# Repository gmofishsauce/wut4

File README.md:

# Wholly Unnecessary Technologies (WUT) model 4 computer (WUT-4 or WUT4)

The content of this repo is [licensed](./LICENSE).

#
## [lang/yasm](./lang/yasm) - wut4 assembler

Assembler written in Go by Claude Code.

## [emul](./emul) - wut4 emulator

Functional emulator written in Go by Claude Code.

## [lang] (./lang) - YAPL language)

Four pass compiler written in Go by Claude Code.

## [exer/cex](./exer/cex) - chip exerciser/tester

CLI tool that communicates via USB serial with a Nano. The Nano
is configured as a chip exerciser / tester. Also in `exer` are
the KiCad schematic for the chip exerciser in `ki` and the Nano
firmware in `fw`. The firmware is a simplified version of the
YARC firmware.

## [lib](./lib)

Eventual library of I/O routines for emulated devices.

## [pld](./pld) - 22v10 experiments

Including a general 8-bit register.

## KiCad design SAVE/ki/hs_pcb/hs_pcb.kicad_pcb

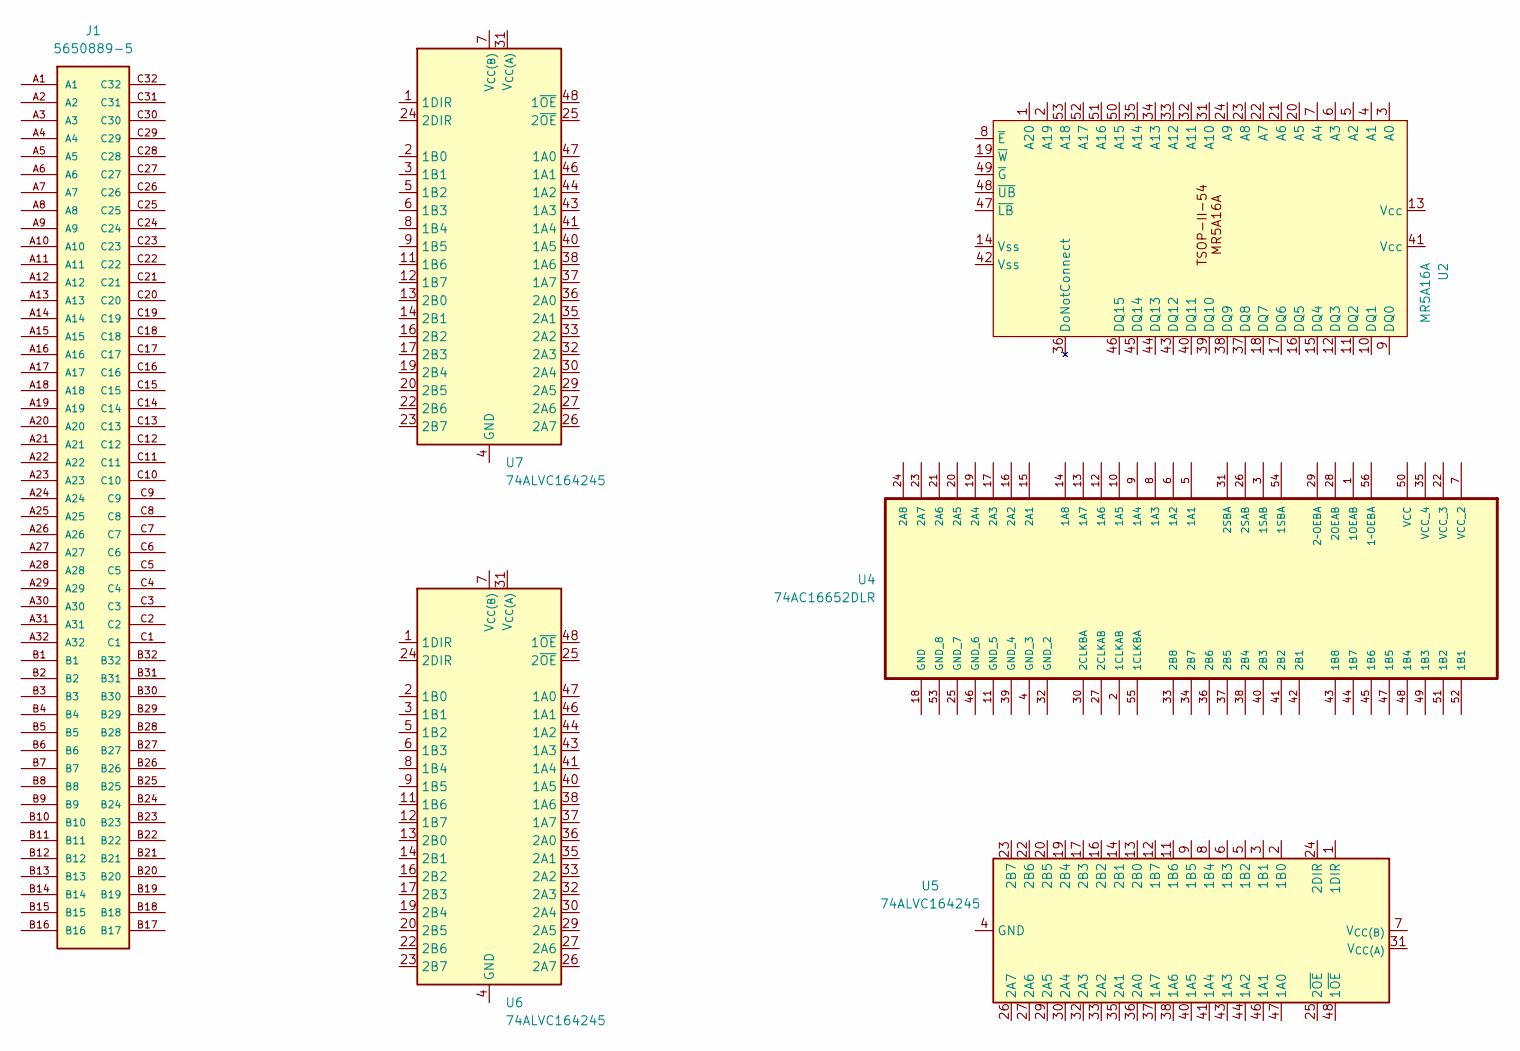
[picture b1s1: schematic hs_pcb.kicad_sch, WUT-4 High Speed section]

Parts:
J1: 5650889-5; TE_5650889-5
U2: MR5A16A; TSOP-II-54_22.2x10.16mm_P0.8mm
U4: 74AC16652DLR; SOP63P1035X279-56N; MPN 74AC16652DLR
U5, U6, U7: 74ALVC164245; TSSOP-48_6.1x12.5mm_P0.5mm

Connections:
unnamed: U5.4 (GND), U5.10 (GND), U5.15 (GND), U5.21 (GND), U5.28 (GND), U5.34 (GND), U5.39 (GND), U5.45 (GND)
unnamed: U5.31 (V_{CC(A)}), U5.42 (V_{CC(A)})
unnamed: U5.7 (V_{CC(B)}), U5.18 (V_{CC(B)})
unnamed: U6.4 (GND), U6.10 (GND), U6.15 (GND), U6.21 (GND), U6.28 (GND), U6.34 (GND), U6.39 (GND), U6.45 (GND)
unnamed: U6.31 (V_{CC(A)}), U6.42 (V_{CC(A)})
unnamed: U6.7 (V_{CC(B)}), U6.18 (V_{CC(B)})
unnamed: U7.4 (GND), U7.10 (GND), U7.15 (GND), U7.21 (GND), U7.28 (GND), U7.34 (GND), U7.39 (GND), U7.45 (GND)
unnamed: U7.31 (V_{CC(A)}), U7.42 (V_{CC(A)})
unnamed: U7.7 (V_{CC(B)}), U7.18 (V_{CC(B)})

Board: 2 copper layers, 7 parts (0 on the bottom side), 9 nets, no tracks yet.

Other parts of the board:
U3: 74AC16652DLR; SOP63P1035X279-56N

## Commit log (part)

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2024-03-11 First step in moving y4 repo to its new home here.
2024-03-11 Second step in conversion. Move assembler, disassembler, and round trip test framework (itf) from the old y4 repo to this repo. Rename disassembler from dis to dsm.
2024-03-11 Step 3 of repo conversion. Add functional emulator and rename it to emul.
2024-03-11 More cleanup on README
2024-03-12 Improve comments and READMEs. Fix call from emulator to disassembler.
2024-03-14 Interim commit - ongoing development
2024-03-15 Ongoing development
2024-03-17 Improve symbol table interface and tests based on some lexer coding. No tests for the lexer yet.
2024-03-18 Add lex_test.go and t1.yapl-1 test program. Add definitions for all the language-defined symbols. Partial implementation of printf(). Update language spec in readme. Other minor changes.
2024-03-19 Many changes required to get basic lexer test to work. Ongoing development.
2024-03-22 Begin parser implementation. Add token pushback.
2024-03-22 Add minimal error handler. Change TT_STR to TT_USR. Clean up AST node handling and add allocator function. Improve logic in first two recursive descent functions. Fix initialization for language symb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
2024-03-23 Move error definitions to error.go. Add a type Error and small functions to handle it. Parser now compiles, but not even close to working. Existing unit tests pass. Add a long comment in types.go.
2024-03-24 Implement better error handler (not tested). Further improve comments.
2024-04-04 Implement types StrIndex and SymIndex. Move code to lex.go from types.go.
2024-04-06 Replace Error type with Word. Get rid of AsError() function. Comment out most of parser and write a simple test for it.
2024-04-14 Parsed a single line after more aimless mucking about with the code
2024-04-15 Change initialization so the descriptor of the (single) source file is passed to the lexer at init and doesn't have to be passed in on each call from the parser.
2024-04-22 Initial KiCad project for wut-4. Includes 2Mx16 MRAM model with TSOP-II 54-pin footprint.
2024-05-20 Initial commit of MR5A16 model in hneeman/Digital
2024-05-25 4-bit synch counter from 1976 TTL Data Book in hnmeeman/Digital
2024-05-28 Remove KiCad backups from repo
2024-05-30 Ongoing development of chip exerciser
2024-06-01 Create exer firmware in fw/ by copying YARC firmware
2024-06-03 Continue removing YARC specifics from serial code for Nano. Begin munging golang code into a single file. FW compiles, Go code does not.
2024-06-04 Continue simplifying protocol
2024-06-04 Continue simplifying code to basic host/nano comms
2024-06-04 rename host side program
2024-06-04 Clean up comments and add cex to gitignore
2024-06-05 This version boots and talks to cex host software. Mostly done removing YARC related code.
2024-06-08 Correct schematic for wiring to the 24-pin socket
2024-06-10 Ongoing development. Nano communicates with host. t (toggle pulse output) command works.
2024-06-11 Protocol v13 adds support for bit reversed set and get. Cex parses arguments in hex now. Move bit reverser in Nano to public. Fix bad debug statement. Lightly tested, quote works endquote.
2024-06-13 Update README with docs for vector-based exerciser
2024-06-14 Hopefully-final fix to U10 control line outputs. They are now on the low-order bits and the Arduino reverses the bits in the register. Also pick up the very start of vector support in host software.
2024-06-16 Update README (still needs work). Temporarily divert main to DoVectorFile() for debugging. Much development in vector.go. Changes to U10 wiring in fact, in KiCad, in Fritzing (separate commit), and m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
2024-06-17 Split out types into separate files. Separate parseVector and applyVector from DoVectorFile. ApplyVector is TODO.
2024-06-18 Move a few things around in search of modularity
2024-06-18 Factor out functions for the t, s, and g commands to the Nano and fix a wiring error in KiCad.
2024-06-18 Reformat the world
2024-06-19 Move Arduino files to local package dev and begin work on applying vectors to hardware
2024-06-24 Correct function (s0..s2) bits in test file and fix bug in flag output processing that caused false error reports.
2024-06-28 Add a summary error count per file and report the total error count for all files. Manually check the sequential test vectors and fix them up to report success when they succeed instead of reporting 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
2024-07-05 Create a 100mm square box and add some 16-bit components
2024-07-18 Complete basic test vectors for L4C381. 4 units passed tests. Improve wiring for 24-pin ZIF socket. Also commit Fritzing changes in $YARC.
2024-07-20 Reformat all the Go code. Improve README. Add top level build script BUILD_ALL.
2024-07-20 Non-overlapping clock generator fails in Digital
2024-07-21 Implement ZIF socket support in cex. Not tested.
2024-07-22 Remove .DS_Store files and add to .gitignore
2024-07-23 Checkpoint - define a PLD and fix test code so that clock is always on pin 1 as required by 22V10 component. Not tested.
2024-07-25 Interim commit after much hardware and software troubleshooting
2024-07-25 Commit 22V574-2 component with a functional test
2024-12-16 Initial commit of new simulator
2024-12-16 Add debugging support
2025-01-23 Ongoing development of C simulator. Create simple PLD for studying 22V10 JEDED files.
2025-01-25 Simplify data structures. Compiles without warnings.
2025-01-25 Freezing sim for more thought
2025-03-02 Move earlier simulators to SAVE/. Add SCsim and learning file first.cpp.
2025-03-03 AI-assisted learning experiment for SystemC simulator
2025-03-18 Give up on SystemC and pull C simulator back out of SAVE/
2025-03-18 Correct previous commit
2025-05-09 Ongoing thinking
2025-05-13 Ongoing work implementing netlist parser for KiCad schematics
2025-05-14 Code now builds and dumps a tree of ModelNodes
2025-05-15 Add a couple of test exports and improve generated top comment
2025-05-18 Interim commit during split of tsp.go into multiple files
2025-05-27 Ongoing development of schematic and transpiler
2025-05-28 Split gen.go source file into bind.go and emit.go
2025-05-28 Complete refactor of gen.go into bind.go and emit.go with GCA
2025-05-28 Exclude binary tsp
2025-06-01 Some work on the emitter. It's all incorrect, yet it's progress.
2025-06-07 Add a bus to the sample data and hack on the code a bit
2025-06-08 Compiles now and generates sensible net macros
2025-06-10 Emit macros for U and Z bits and also for buses
2025-06-10 Split utilities out of emit.go into emitUtils.go
2025-06-12 Add emitter for types, remove blank lines from output, remove debug
2025-06-13 Begin work on C language simulation to direct transpiler improvements
2025-07-11 Minor changes refamiliarizing after a long break from this code
2025-07-12 Writing the full simulator by hand first
2025-07-15 The key macros GETBITS() and SETBITS() appear to work now.
2025-07-16 Continuing development of macros for use in resolver functions.
2025-07-17 GETSIB and SETSIB macros and friends in (hopefully) final form
2025-07-18 Remove unnecessary backup files
2025-07-18 git ignore backup KiCad files
2025-07-19 Additional cleanup and removal of unused generated code
2025-07-19 Fill out the rest of the sample simulation with API
2025-07-23 Now write a NetList.csv file defining all the signals for tracing purposes (TBD)
2025-07-23 Checkpoint during implementation of tracing
2025-07-24 Revise strategy for core access to transpiler generated data
2025-07-25 Teach the transpiler about the revised strategy
2025-07-25 Rename tsp directory to SINTER. Remove noise for B script. Begin creation of VCD writer in WV.
2025-07-25 Rename sinter back to tsp and fix up .gitignore again.
2025-07-26 wv now writes a VCD header that 'vcd' accepts
2025-07-26 move simulator core to CORE/ and update README with aspirational description
2025-07-26 Fix bugs caused by moving some files around
2025-07-26 Ooops, add the gitignore
2025-07-27 Table-driven inline 4-state logic functions added to API
2025-07-28 Use 'generate' instead of 'emit' in messages so the code doesn't have emissions.
2025-12-16 fixups in the assembler (not tested)
2025-12-16 add copy of arch document for use by Claude
2025-12-18 some work on the assembler.
2025-12-22 fix several bugs in the assembler and in the emulate
2025-12-25 more commits from claude
2025-12-27 trying to debug character input and output but failing
2025-12-28 Vibe coded assembler with specs and prompt
2025-12-28 Claude-coded assembler
2025-12-30 integrate specification changes in wut4asm.pdf
2025-12-31 have Claude fix some of its own bugs
2025-12-31 add tests
2026-01-03 update arch doc with UART emulator spec
2026-01-04 add UART emulator coded by Claude along with the prompt and some other documentation
2026-01-04 get Claude to fix Consol slop at start up, and update spec for UART interrupts.
2026-01-05 clean up and remove some steel files move other files around. No new code
2026-01-20 add README and apdf doc copy of some words about YAPL.
2026-01-23 commit lexical analyzer and parser written by Claude code with my help
2026-01-25 add a test for a string initialization and add the #asm()keyword.
2026-01-26 improve string initialization in yapl
2026-01-26 convert to mod files (straighten out build)
2026-01-26 fix gitignore for changed binary names
2026-01-27 add code generator (gen) written by Claude
2026-01-27 type system fix for decaying arrays to pointers from Claude
2026-01-28 reordered initialization. Reject zero-code binaries. Explicit restoreTerminal() after emulation. Fixed by Claude.
2026-01-28 fix accidental commit of gen binary
2026-01-28 1. sem/ir.go - Byte pointer dereference used LOAD.W instead of LOAD.BU - @bp where bp is @byte now correctly loads a byte, not a word 2. gen/codegen.go - genJumpZ/genJumpNZ - Used tst r4, r4 which al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
2026-01-29 rename the lexer to avoid conflict with /usr/bin/lex
2026-01-29 write a standard driver for the compiler (Claude)
2026-01-29 rename all the binaries because their names were too generic and could conflict with system programs
2026-02-11 fixes by Claude
2026-02-12 complete this round of compiler fixes from Claude
2026-02-12 claude: add test and fix bugs in code generation.
2026-02-13 Claude rename asm to yasm.
2026-02-13 compiler fixes from the new test program
2026-02-13 Claude: add support for #pragma bootstrap
2026-02-17 a couple of changes, really hacks, to deal with long branches.
2026-02-17 add some tests. Some tests have to do with working on the SD card emulator. Others have to do with reviewing the code after I learned how to better do this from a YouTube video
2026-02-17 fix bugs found by Claude in code review mode. The tests in the previous commit were regressions for these bugs so the previous commit does not compile cleanly, or at least, does not test clean.
2026-02-18 Update build script to run tests before installing
2026-02-22 fix by Claude for type compatibility of &arr with pointer to element
2026-02-23 remove earlier attempt at an I/O library
2026-02-23 add Claude's review and a test written during the review. Also add Claude's fixes to the review-role comments.
2026-02-24 commit a compiler change by Claude and a test that Claude couldn't get to work.
2026-02-25 Claude: add boot.asm at my very explicit direction and modify the compiler to use it appropriately. Improve the build script. Fix a test. Move some document we file surround and remove some steel fil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
2026-02-26 add a script to clean up the test directory and do so.
2026-02-27 fix compiler bugs
2026-02-27 clean up garbage
2026-03-03 Claude fix bootstrap trampoline strategy
2026-03-03 Claude makes a bunch more fixes for bootstrapping
2026-06-01 cleanup and corrections
2026-06-02 Claude write design file
2026-06-02 capture development artifact and latest status
2026-06-05 Claude fix some visual issues in the editor
2026-06-10 findings and tests from review by Claude Fable
2026-06-11 Claude: write interpretive simulator
2026-06-12 Claude: fix bug with changing filename on save
